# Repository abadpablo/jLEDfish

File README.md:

# jLEDFish

Welcome to the jellyFish repository!

This repository contains an Eagle project to design and build a PCB board for optogenetic stimulation

## Authors
Juan Pablo Quintanilla, Pablo Abad and Manuel Valero

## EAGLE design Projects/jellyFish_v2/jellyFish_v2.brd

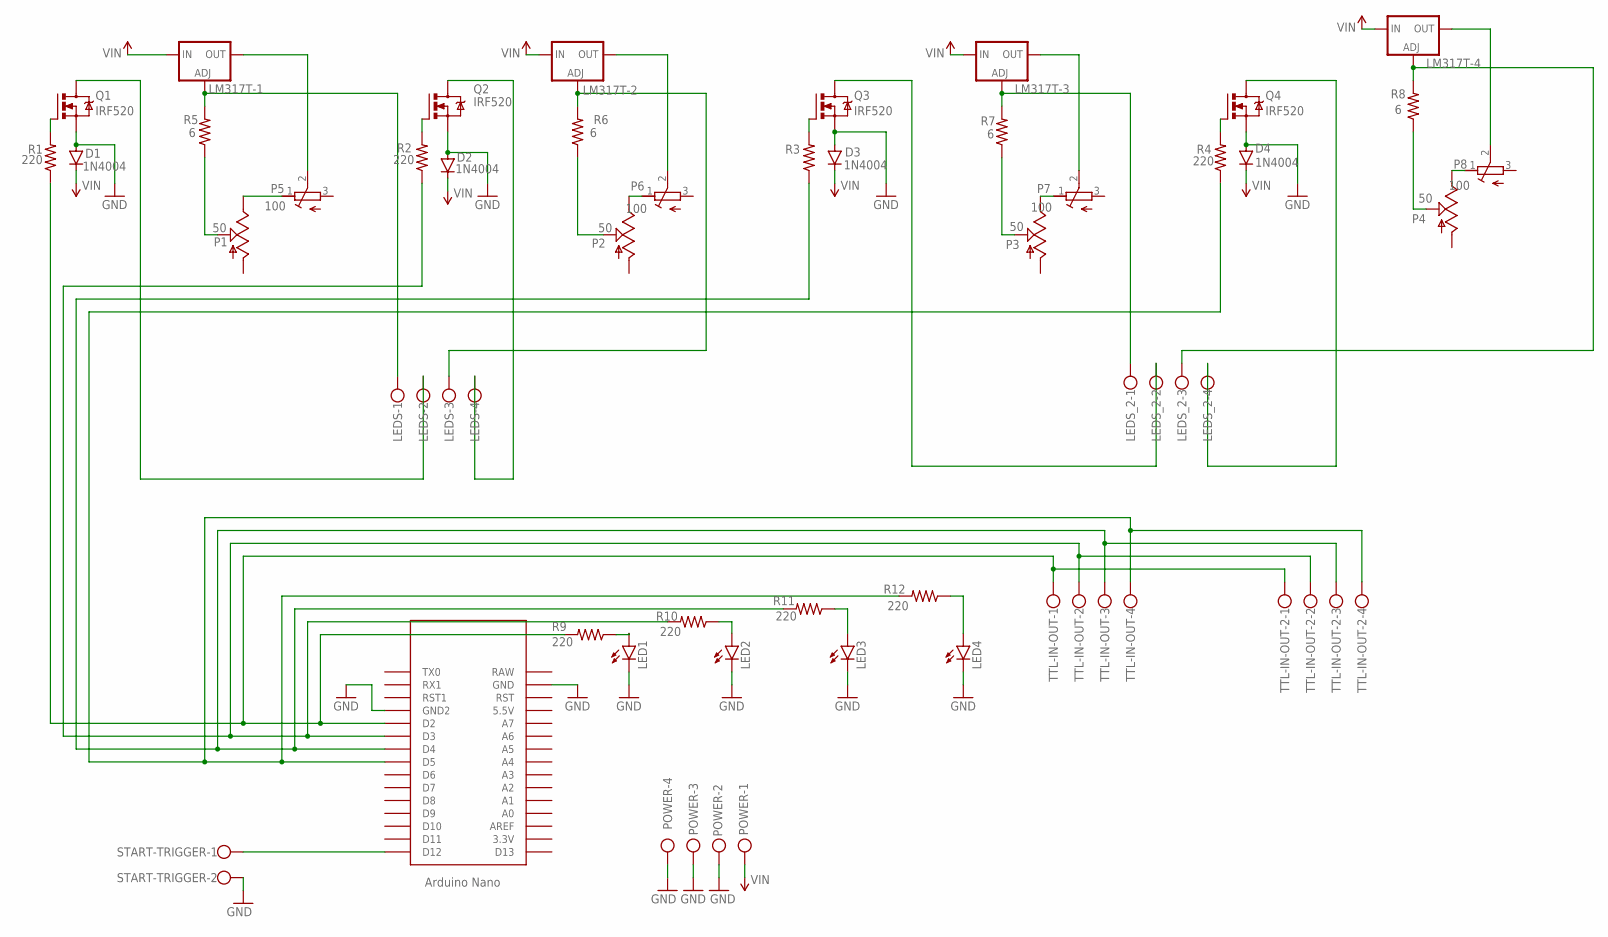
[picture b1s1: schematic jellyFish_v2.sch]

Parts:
D1, D2, D3, D4: 1N4004; DO41-10
LED1, LED2, LED3, LED4: LEDCHIPLED_0805; CHIPLED_0805
LEDS: W237-4
LEDS_2: W237-4
LM317T-1, LM317T-2, LM317T-3, LM317T-4: LM317TS; 317TS
P1, P2, P3, P4: 50; S63P
P5, P6, P7, P8: 100; RTRIMT93YA
POWER: W237-4
Q1, Q2, Q3, Q4: IRF520; TO220BV
R1, R2, R3, R4, R9, R10, R11, R12: 220; R0805
R5, R6, R7, R8: 6; R0805
START-TRIGGER: W237-102
TTL-IN-OUT: W237-4
TTL-IN-OUT-2: W237-4
U$1: NANO

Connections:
GND: D1.A, D2.A, D3.A, D4.A, LED1.C, LED2.C, LED3.C, LED4.C, POWER.2, POWER.3, POWER.4, Q1.S, Q2.S, Q3.S, Q4.S, START-TRIGGER.2, U$1.GND, U$1.GND1 (GND2)
unnamed: P3.E, P7.1 (E)
unnamed: Q1.G, R1.2
unnamed: R1.1, R9.2, TTL-IN-OUT.1, TTL-IN-OUT-2.1, U$1.D2
unnamed: Q2.G, R2.2
unnamed: P2.E, P6.1 (E)
unnamed: R2.1, R10.2, TTL-IN-OUT.2, TTL-IN-OUT-2.2, U$1.D3
unnamed: LEDS_2.1, LM317T-3.1 (ADJ), R7.2
unnamed: LEDS.3, LM317T-2.1 (ADJ), R6.2
unnamed: Q3.G, R3.2
unnamed: R3.1, R11.2, TTL-IN-OUT.3, TTL-IN-OUT-2.3, U$1.D4
unnamed: P3.S, R7.1
unnamed: P4.E, P8.1 (E)
unnamed: P2.S, R6.1
unnamed: LM317T-3.2 (OUT), P7.2 (S)
unnamed: P1.E, P5.1 (E)
unnamed: P1.S, R5.1
unnamed: P4.S, R8.1
unnamed: LM317T-2.2 (OUT), P6.2 (S)
unnamed: LEDS.2, Q1.D
unnamed: LEDS.4, Q2.D
unnamed: START-TRIGGER.1, U$1.D12
unnamed: Q4.G, R4.2
unnamed: R4.1, R12.2, TTL-IN-OUT.4, TTL-IN-OUT-2.4, U$1.D5
unnamed: LEDS_2.2, Q3.D
unnamed: LEDS_2.3, LM317T-4.1 (ADJ), R8.2
unnamed: LM317T-4.2 (OUT), P8.2 (S)
unnamed: LM317T-1.2 (OUT), P5.2 (S)
unnamed: LEDS_2.4, Q4.D
unnamed: LED1.A, R9.1
unnamed: LED2.A, R10.1
unnamed: LED3.A, R11.1
unnamed: LED4.A, R12.1
unnamed: LEDS.1, LM317T-1.1 (ADJ), R5.2
VIN: D1.C, D2.C, D3.C, D4.C, LM317T-1.3 (IN), LM317T-2.3 (IN), LM317T-3.3 (IN), LM317T-4.3 (IN), POWER.1

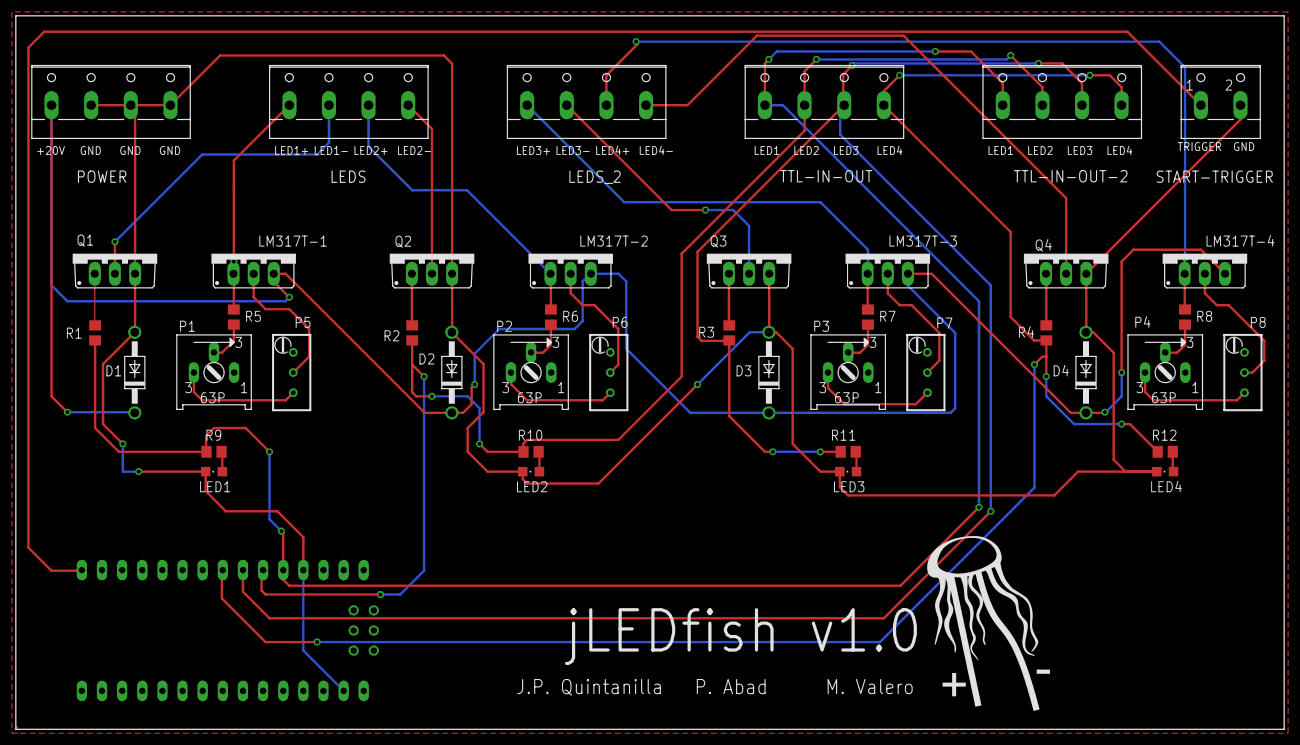
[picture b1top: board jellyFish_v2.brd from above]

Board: 2 copper layers, 160.0 x 90.0 mm, 43 parts (0 on the bottom side), 35 nets.

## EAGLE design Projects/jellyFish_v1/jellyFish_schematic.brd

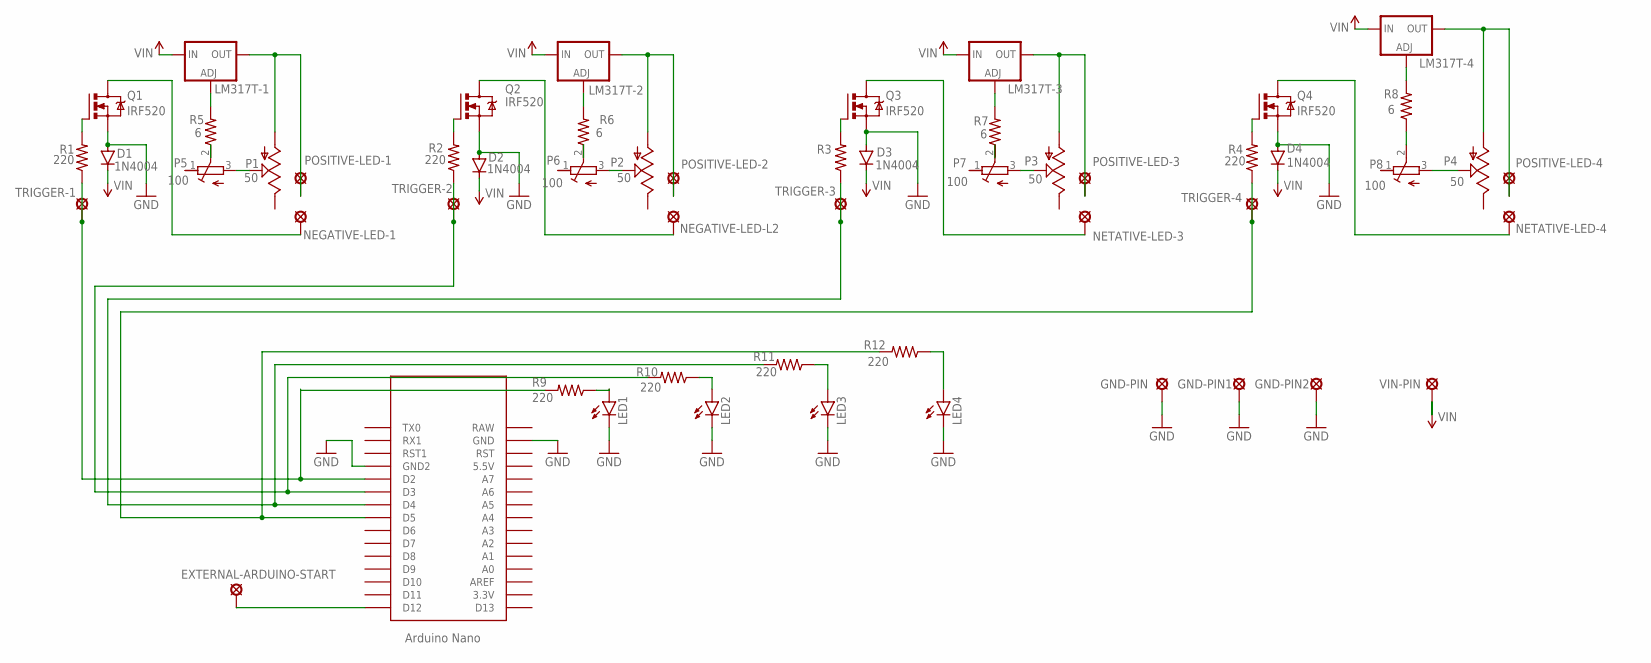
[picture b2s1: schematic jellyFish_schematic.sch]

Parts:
D1, D2, D3, D4: 1N4004; DO41-10
EXTERNAL-ARDUINO-START: LSP10
GND-PIN, GND-PIN1, GND-PIN2: LSP10
LED1, LED2, LED3, LED4: LEDCHIPLED_0805; CHIPLED_0805
LM317T-1, LM317T-2, LM317T-3, LM317T-4: LM317TS; 317TS
NEGATIVE-LED-1: LSP10
NEGATIVE-LED-L2: LSP10
NETATIVE-LED-3, NETATIVE-LED-4: LSP10
P1, P2, P3, P4: 50; S63P
P5, P6, P7, P8: 100; RTRIMT93YA
POSITIVE-LED-1: POSITIVE LED; LSP10
POSITIVE-LED-2, POSITIVE-LED-3, POSITIVE-LED-4: LSP10
Q1, Q2, Q3, Q4: IRF520; TO220BV
R1, R2, R3, R4, R9, R10, R11, R12: 220; R0805
R5, R6, R7, R8: 6; R0805
TRIGGER-1, TRIGGER-2, TRIGGER-3, TRIGGER-4: LSP10
U$1: NANO
VIN-PIN: LSP10

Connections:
GND: D1.A, D2.A, D3.A, D4.A, GND-PIN.MP, GND-PIN1.MP, GND-PIN2.MP, LED1.C, LED2.C, LED3.C, LED4.C, Q1.S, Q2.S, Q3.S, Q4.S, U$1.GND, U$1.GND1 (GND2)
unnamed: NEGATIVE-LED-1.MP, Q1.D
unnamed: Q1.G, R1.2
unnamed: R1.1, R9.2, TRIGGER-1.MP, U$1.D2
unnamed: Q2.G, R2.2
unnamed: P6.2 (S), R6.1
unnamed: R2.1, R10.2, TRIGGER-2.MP, U$1.D3
unnamed: LM317T-3.1 (ADJ), R7.2
unnamed: LM317T-2.1 (ADJ), R6.2
unnamed: Q3.G, R3.2
unnamed: R3.1, R11.2, TRIGGER-3.MP, U$1.D4
unnamed: P7.2 (S), R7.1
unnamed: P3.S, P7.3 (A)
unnamed: LM317T-1.1 (ADJ), R5.2
unnamed: LM317T-3.2 (OUT), P3.A, POSITIVE-LED-3.MP
unnamed: P1.S, P5.3 (A)
unnamed: LM317T-1.2 (OUT), P1.A, POSITIVE-LED-1.MP
unnamed: P2.S, P6.3 (A)
unnamed: LM317T-2.2 (OUT), P2.A, POSITIVE-LED-2.MP
unnamed: NEGATIVE-LED-L2.MP, Q2.D
unnamed: NETATIVE-LED-3.MP, Q3.D
unnamed: Q4.G, R4.2
unnamed: R4.1, R12.2, TRIGGER-4.MP, U$1.D5
unnamed: NETATIVE-LED-4.MP, Q4.D
unnamed: LM317T-4.1 (ADJ), R8.2
unnamed: P8.2 (S), R8.1
unnamed: P4.S, P8.3 (A)
unnamed: LM317T-4.2 (OUT), P4.A, POSITIVE-LED-4.MP
unnamed: LED1.A, R9.1
unnamed: LED2.A, R10.1
unnamed: LED3.A, R11.1
unnamed: LED4.A, R12.1
unnamed: EXTERNAL-ARDUINO-START.MP, U$1.D12
P5: P5.2 (S), R5.1
VIN: D1.C, D2.C, D3.C, D4.C, LM317T-1.3 (IN), LM317T-2.3 (IN), LM317T-3.3 (IN), LM317T-4.3 (IN), VIN-PIN.MP

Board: 2 copper layers, 54 parts (0 on the bottom side), 35 nets, no tracks yet.

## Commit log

2022-04-30 ¨NewFolders¨
2022-04-30 ¨Default¨
2022-05-01 ¨LED¨
2022-05-02 Added Trigger Outputs
2022-05-03 adding logo files
2022-05-03 Added Logo

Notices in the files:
parts and their libraries:
SparkFun-PowerSymbols: Licensing: Creative Commons ShareAlike 4.0 International - https://creativecommons.org/licenses/by-sa/4.0
